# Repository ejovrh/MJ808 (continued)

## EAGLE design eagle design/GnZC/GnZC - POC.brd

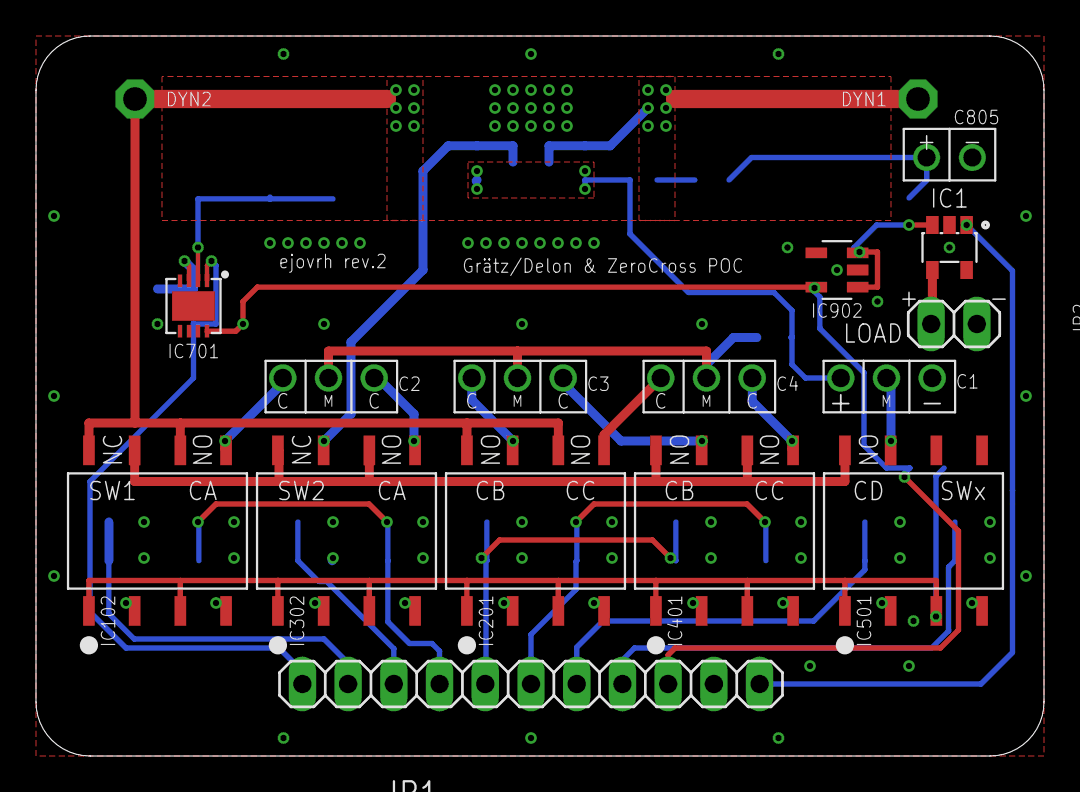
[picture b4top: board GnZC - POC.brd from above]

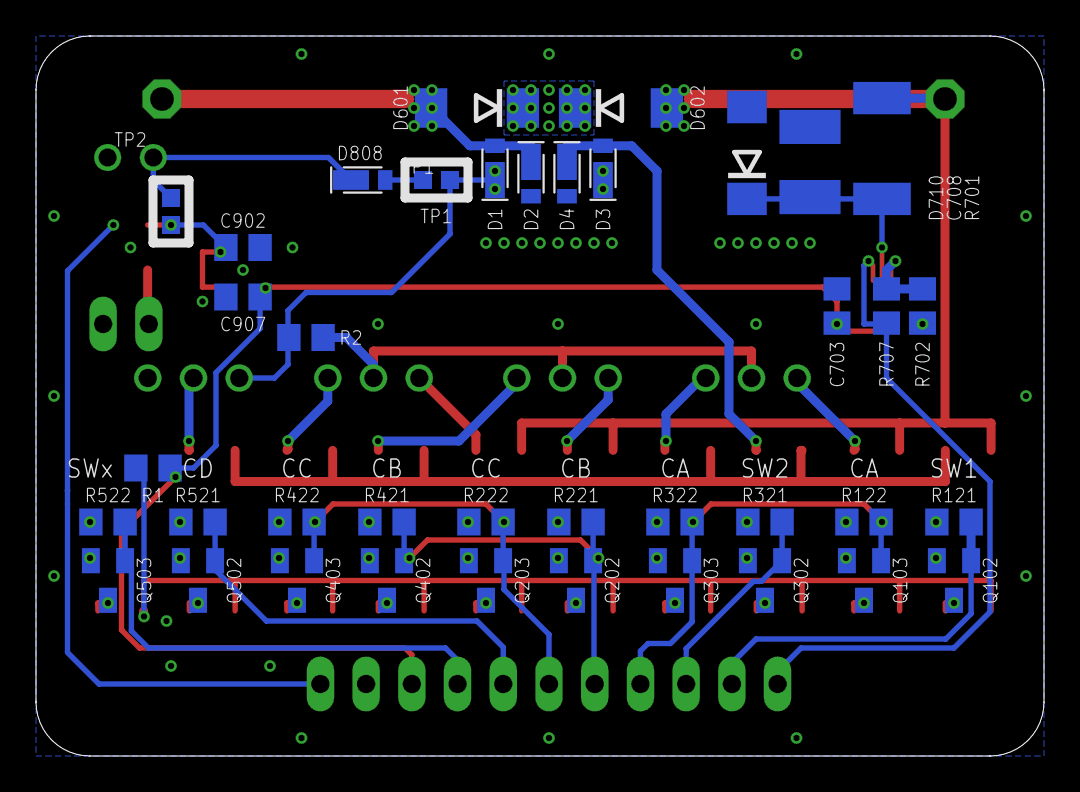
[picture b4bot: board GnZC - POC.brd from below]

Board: 2 copper layers, 56.0 x 40.0 mm, 58 parts (41 on the bottom side), 42 nets.

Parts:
C1: 330μF / 35V / ultralow ESR; TH-2S
C2, C3, C4: 1500μF / 35V / ultralow ESR; TH-2S-BACK-TO-BACK
C703: 0.1uF / 10V; C0805
C708: 10nF / 100v; C1812
C805: 2P 4700μF / 35V / ultralow ESR; TH
C902, C907: 1uF / 10V; C0805
D1, D2, D3, D4, D808: CUHS20S30,H3F; US2H
D601, D602: 19V/5W; DO214AA
D710: 6V/3W; DO214AA
IC1: MIC2514YM5; SOT-23-5
IC102, IC302: LBA710S; SMD_DIP8
IC201, IC401, IC501: LAA710S; SMD_DIP8
IC701: LT1638IDD#PBF; DFN-8
IC902: LDK320AM33R; SOT-23-5L
JP1: out; 1X11
JP2: 2.54-pinhead; 1X02
Q102, Q103, Q202, Q203, Q302, Q303, Q402, Q403, Q502, Q503: IRLML2402TRPBF; SOT23
R1: 430R/0.5W; R0805
R2: 47k; R0805
R121, R122, R221, R222, R321, R322, R421, R422, R521, R522, R702, R707: 10k; R0805
R701: 10k/3W; R2512
TP2: dynamo 1; P1-13
TP3: dynamo 2; P1-13
TP4: TP1l; TP10SQ
TP5: TP1r; TP10SQ
TP6: TP2l; TP10SQ
TP7: TP2r; TP10SQ

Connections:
+3V3: C703.2, C907.2, IC701.8_V+, IC902.OUT, JP1.9, R1.2
CAA: C2.1_C, IC102.5_DRAIN2-1
CAB: C2.3_C, IC302.5_DRAIN2-1
CBA: C3.1_C, IC201.7_DRAIN1-1
CBB: C3.3_C, IC401.7_DRAIN1-1
CCA: C4.1_C, IC201.5_DRAIN2-1
CCB: C4.3_C, IC401.5_DRAIN2-1
DYNAMO1: D1.C, D2.A, D601.A, TP2.TP
DYNAMO2_AFTER_TUNING-CAP_SW: IC102.7_DRAIN1-1, IC302.6_DRAIN2-2, IC302.8_DRAIN1-2, IC401.6_DRAIN2-2, IC401.8_DRAIN1-2, IC501.8_DRAIN1-2
DYNAMO2_BEFORE_TUNING-CAP_SW: D602.A, IC102.6_DRAIN2-2, IC102.8_DRAIN1-2, IC201.6_DRAIN2-2, IC201.8_DRAIN1-2, R701.1, TP3.TP
DYNAMO2_DELON: C1.2_MID, IC501.7_DRAIN1-1
DYNAMO2_GRAETZ: D3.C, D4.A, IC302.7_DRAIN1-1
GND: C1.3_NEG, C703.1, C708.1, C805.NEG, C902.2, C907.1, D2.C, D4.C, D710.A, IC1.P$2, IC701.4_V-, IC701.9_V-, IC902.GND, JP1.10, JP2.2, Q102.2, Q103.2, Q202.2, Q203.2, Q302.2, Q303.2, Q402.2, Q403.2, Q502.2, Q503.2, R121.2, R122.2, R221.2, R222.2, R321.2, R322.2, R421.2, R422.2, R521.2, R522.2, R702.1
LOAD_HIGHSIDE: IC1.P$4, JP2.1
LOAD_SWITCH: IC1.P$1, JP1.11
OVP:ZENER_COMMON: D601.C, D602.C
SSR_ANODE: IC102.1_ANODE1, IC102.3_ANODE2, IC201.1_ANODE1, IC201.3_ANODE2, IC302.1_ANODE1, IC302.3_ANODE2, IC401.1_ANODE1, IC401.3_ANODE2, IC501.1_ANODE1, IC501.3_ANODE2, R1.1
SSR_NC/NO1:SW1_CAT: IC102.2_CATHODE1, Q102.3
SSR_NC/NO1:SW2_CAT: IC102.4_CATHODE2, Q103.3
SSR_NC/NO2:SW1_CAT: IC302.2_CATHODE1, Q302.3
SSR_NC/NO2:SW2_CAT: IC302.4_CATHODE2, Q303.3
SSR_NO/NO1:SW1_CAT: IC201.2_CATHODE1, Q202.3
SSR_NO/NO1:SW2_CAT: IC201.4_CATHODE2, Q203.3
SSR_NO/NO2:SW1_CAT: IC401.2_CATHODE1, Q402.3
SSR_NO/NO2:SW2_CAT: IC401.4_CATHODE2, Q403.3
SSR_NO/NO3:SW1_CAT: IC501.2_CATHODE1, Q502.3
SSR_NO/NO3:SW2_CAT: IC501.4_CATHODE2, Q503.3
SW1_CTRL: JP1.2, Q102.1, R121.1
SW2_CTRL: JP1.3, Q302.1, R321.1
SW_CA_CTRL: JP1.4, Q103.1, Q303.1, R122.1, R322.1
SW_CB_CTRL: JP1.5, Q202.1, Q402.1, R221.1, R421.1
SW_CC_CTRL: JP1.6, Q203.1, Q403.1, R222.1, R422.1
SW_CD_CTRL: JP1.7, Q502.1, R521.1
SW_X_CTRL: JP1.8, Q503.1, R522.1
TUNING_CAP_BIAS: C2.2_MID, C3.2_MID, C4.2_MID, R2.1
V_RECT_TP1-IN: C1.1_POS, D1.A, D3.A, R2.2, TP4.TP
V_RECT_TP1-OUT: D808.C, TP5.TP
V_REGULATED_TP2-IN: C805.POS, D808.A, TP6.TP
V_REGULATED_TP2-OUT: C902.1, IC1.P$3, IC902.EN, IC902.IN, TP7.TP
ZERO-CROSS_DETECTOR:N$6: C708.2, D710.C, IC701.2_A_IN-, R701.2
ZERO-CROSS_DETECTOR:N$12: IC701.3_A_IN+, R702.2, R707.2
ZEROCROSS: IC701.1_A_OUT, JP1.1, R707.1

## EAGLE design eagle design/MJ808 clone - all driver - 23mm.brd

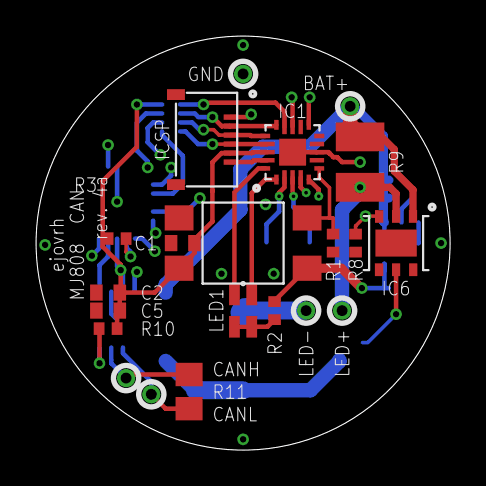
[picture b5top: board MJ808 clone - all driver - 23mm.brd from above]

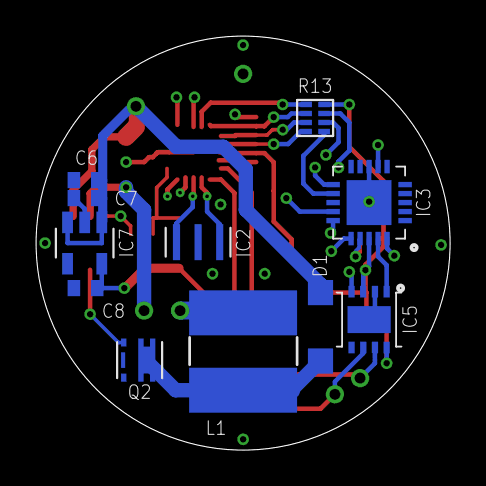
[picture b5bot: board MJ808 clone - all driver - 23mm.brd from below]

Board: 2 copper layers, 23.0 x 23.0 mm, 32 parts (11 on the bottom side), 30 nets.

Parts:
BAT+: LiIon + Terminal; TH
C1, C2, C5: 0.1μF; C0402
C6, C7: 1μF / 10V; C0402
C8: 1μF; C0402
CANH: CAN high; TH
CANL: CAN low; TH
D1: PMEG2010ER,115; SOD123
GND: LiIon - Terminal; TH
IC1: ATTINY4313-MMH; VQFN-20
IC2: PRQV8.00CR1510Y00L; SMT
IC3: MCP2515; QFN20
IC5: MCP2561-2; DFN10
IC6: MAX16820; TDFN-6-EP
IC7: LDK320ADU50R; SOT-23-5L
ICSP: 5034800600; SMT
L1: VLS6045EX-150M-CA - 15uH; SRN6045
LED1: APHBM2012LSURKZGKC; SMD
LED+: LED anode; TH
LED-: LED cathode; TH
Q2: SiA456DJ; SC-70-6
R1, R2, R3, R8, R10: 10k; R0402
R9: 0.15 / 1W; R1210
R11: 120; R0805
R13: 741X083331JP 330R; 0402
SW1: TL3305-844809; SMD

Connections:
5V0: C1.1, C2.1, C5.1, C8.2, IC1.18, IC3.VDD, IC5.VDD, IC7.OUT, ICSP.5, R2.2, R3.1, R10.1, R13.8, SW1.1, SW1.2
BAT+: BAT+.TP$1, C6.1, C7.1, D1.C, IC6.IN, IC7.EN, IC7.IN, R9.2
CANH: CANH.TP$1, IC5.CANH, R11.2
CANL: CANL.TP$1, IC5.CANL, R11.1
CLOCKOUT: IC1.4, IC3.OSC1
DEBUGWIRE/RESET: IC1.19, ICSP.6
DIM_FRONT: IC1.13, IC6.DIM, R8.1
DIM_FRONT_DRAIN: D1.A, L1.1, Q2.1D, Q2.2D, Q2.5D, Q2.6D, Q2.D
DIM_FRONT_GATE: IC6.DRV, Q2.3G
GND: C1.2, C2.2, C5.2, C6.2, C7.2, C8.1, GND.TP$1, IC1.8, IC1.GND, IC2.GND, IC3.GND, IC3.GND6, IC5.GND, IC5.VSS, IC6.GND, IC6.GND1, IC7.GND, ICSP.1, ICSP.GND1, ICSP.GND2, Q2.4S, Q2.S, R1.2, R8.2
GREEN_LED: IC1.20, LED1.3
ICSP_DI/MISO: IC1.15, ICSP.2, R13.5
ICSP_DO/MOSI: IC1.16, ICSP.3, R13.3
ICSP_SCK: IC1.17, ICSP.4, R13.1
INT: IC1.5, IC3.!INT!
LED: LED1.1, LED1.4, R2.1
LED_AN: IC6.CSN, LED+.TP$1, R9.1
LED_CA: L1.2, LED-.TP$1
RED_LED: IC1.1, LED1.2
RESET: IC3.!RESET!, R3.2
RXCAN: IC3.RXCAN, IC5.RXD
SPI_MISO: IC3.SO, R13.6
SPI_MOSI: IC3.SI, R13.4
SPI_SCK: IC3.SCK, R13.2
SPI_SS: IC1.14, IC3.!CS!, R13.7
STBY: IC1.11, IC5.STBY, R10.2
SWITCH: IC1.6, R1.1, SW1.3, SW1.4
TXCAN: IC3.TXCAN, IC5.TXD
XTAL1: IC1.3, IC2.XTAL1
XTAL2: IC1.2, IC2.XTAL2

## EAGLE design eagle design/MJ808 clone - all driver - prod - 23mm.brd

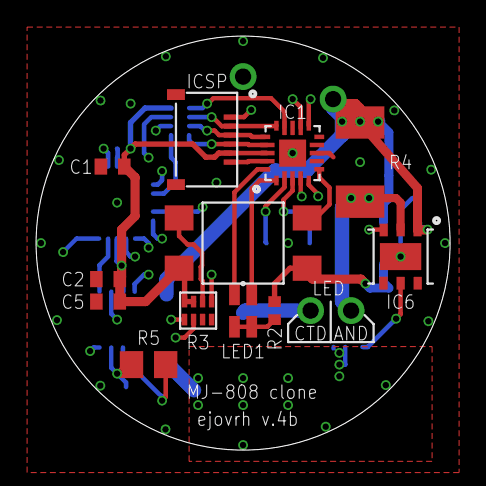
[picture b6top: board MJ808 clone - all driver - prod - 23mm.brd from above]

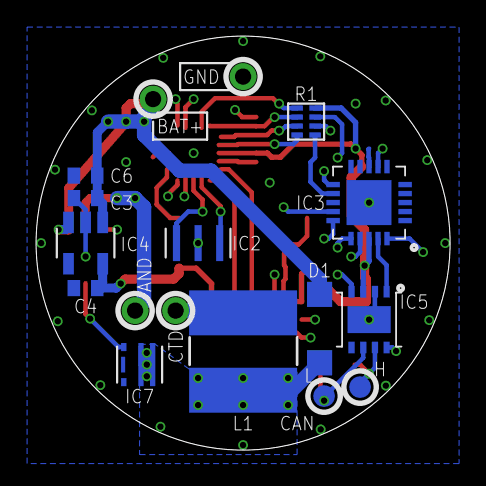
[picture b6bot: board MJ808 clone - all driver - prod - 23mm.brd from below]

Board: 4 copper layers, 23.0 x 23.0 mm, 29 parts (17 on the bottom side), 30 nets.

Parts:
AND: LED anode; TH-0.9MM
BAT+: LiIon + Terminal; TH-0.9MM
C1, C2, C5: 0.1μF; C0402
C3, C6: 1μF / 10V; C0402
C4: 1μF; C0402
CTD: LED cathode; TH-0.9MM
D1: PMEG2010ER,115; SOD123
GND: LiIon - Terminal; TH-0.9MM
H: CAN high; SMT-1.2MM
IC1: ATTINY4313-MMH; VQFN-20
IC2: PBRC8.00GR50X000; SMT
IC3: MCP2515; QFN20
IC4: LDK320M50R; SOT-23-5L
IC5: MCP2561-2; DFN10
IC6: MAX16820; TDFN-6-EP
IC7: SQA470EEJ-T1_GE3; SC-70-6
ICSP: 5034800600; SMT
L: CAN low; SMT-1.2MM
L1: VLS6045EX-150M-CA - 15uH; SRN6045
LED1: IN-S85DATRG; SMD
R1: 741X083331JP 330R; 0402-4R
R2: 10k; R0402
R3: 741X083103JP 10k; 0402-4R
R4: WSLT2010R2200FEB18 / 0.22Ohm 1W; R2010
R5: 120; R0805
SW1: TL3305CF160QG; SMD

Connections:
5V0: C1.1, C2.1, C4.2, C5.1, IC1.18, IC3.VDD, IC4.OUT, IC5.VDD, ICSP.5, R1.8, R2.2, R3.6, R3.8, SW1.1, SW1.2
BAT+: BAT+.TP$1, C3.1, C6.1, D1.C, IC4.EN, IC4.IN, IC6.IN, R4.2
CANH: H.P$1, IC5.CANH, R5.2
CANL: IC5.CANL, L.P$1, R5.1
CLOCKOUT: IC1.4, IC3.OSC1
DEBUGWIRE/RESET: IC1.19, ICSP.6
DIM_FRONT: IC1.12, IC6.DIM, R3.2
DIM_FRONT_DRAIN: D1.A, IC7.1D, IC7.2D, IC7.5D, IC7.6D, IC7.D, L1.1
DIM_FRONT_GATE: IC6.DRV, IC7.3G
GND: C1.2, C2.2, C3.2, C4.1, C5.2, C6.2, GND.TP$1, IC1.8, IC1.GND, IC2.GND, IC3.GND, IC3.GND6, IC4.GND, IC5.GND, IC5.VSS, IC6.GND, IC6.GND1, IC7.4S, IC7.S, ICSP.1, ICSP.GND1, ICSP.GND2, R3.1, R3.3
GREEN_LED: IC1.20, LED1.3
ICSP_DI/MISO: IC1.15, ICSP.2, R1.5
ICSP_DO/MOSI: IC1.16, ICSP.3, R1.3
ICSP_SCK: IC1.17, ICSP.4, R1.1
INT: IC1.5, IC3.!INT!
LED: LED1.1, LED1.4, R2.1
LED_AN: AND.TP$1, IC6.CSN, R4.1
LED_CA: CTD.TP$1, L1.2
RED_LED: IC1.1, LED1.2
RESET: IC3.!RESET!, R3.5
RXCAN: IC3.RXCAN, IC5.RXD
SPI_MISO: IC3.SO, R1.6
SPI_MOSI: IC3.SI, R1.4
SPI_SCK: IC3.SCK, R1.2
SPI_SS: IC1.14, IC3.!CS!, R1.7
STBY: IC1.11, IC5.STBY, R3.7
SWITCH: IC1.6, R3.4, SW1.3, SW1.4
TXCAN: IC3.TXCAN, IC5.TXD
XTAL1: IC1.3, IC2.XTAL1
XTAL2: IC1.2, IC2.XTAL2
